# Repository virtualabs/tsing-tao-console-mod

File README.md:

# Tsing Tao v1 - a cheap ESP32 mod for a cheap handheld

Tsing Tao is a set of three tiny printed circuit boards that can turn any cheap
Chinese handheld gaming console (sold as Game Boy like console with 400+ NES
games) into a full-featured retro emulator able to run GameBoy, Game Gear, NES,
and Master System ROMs.

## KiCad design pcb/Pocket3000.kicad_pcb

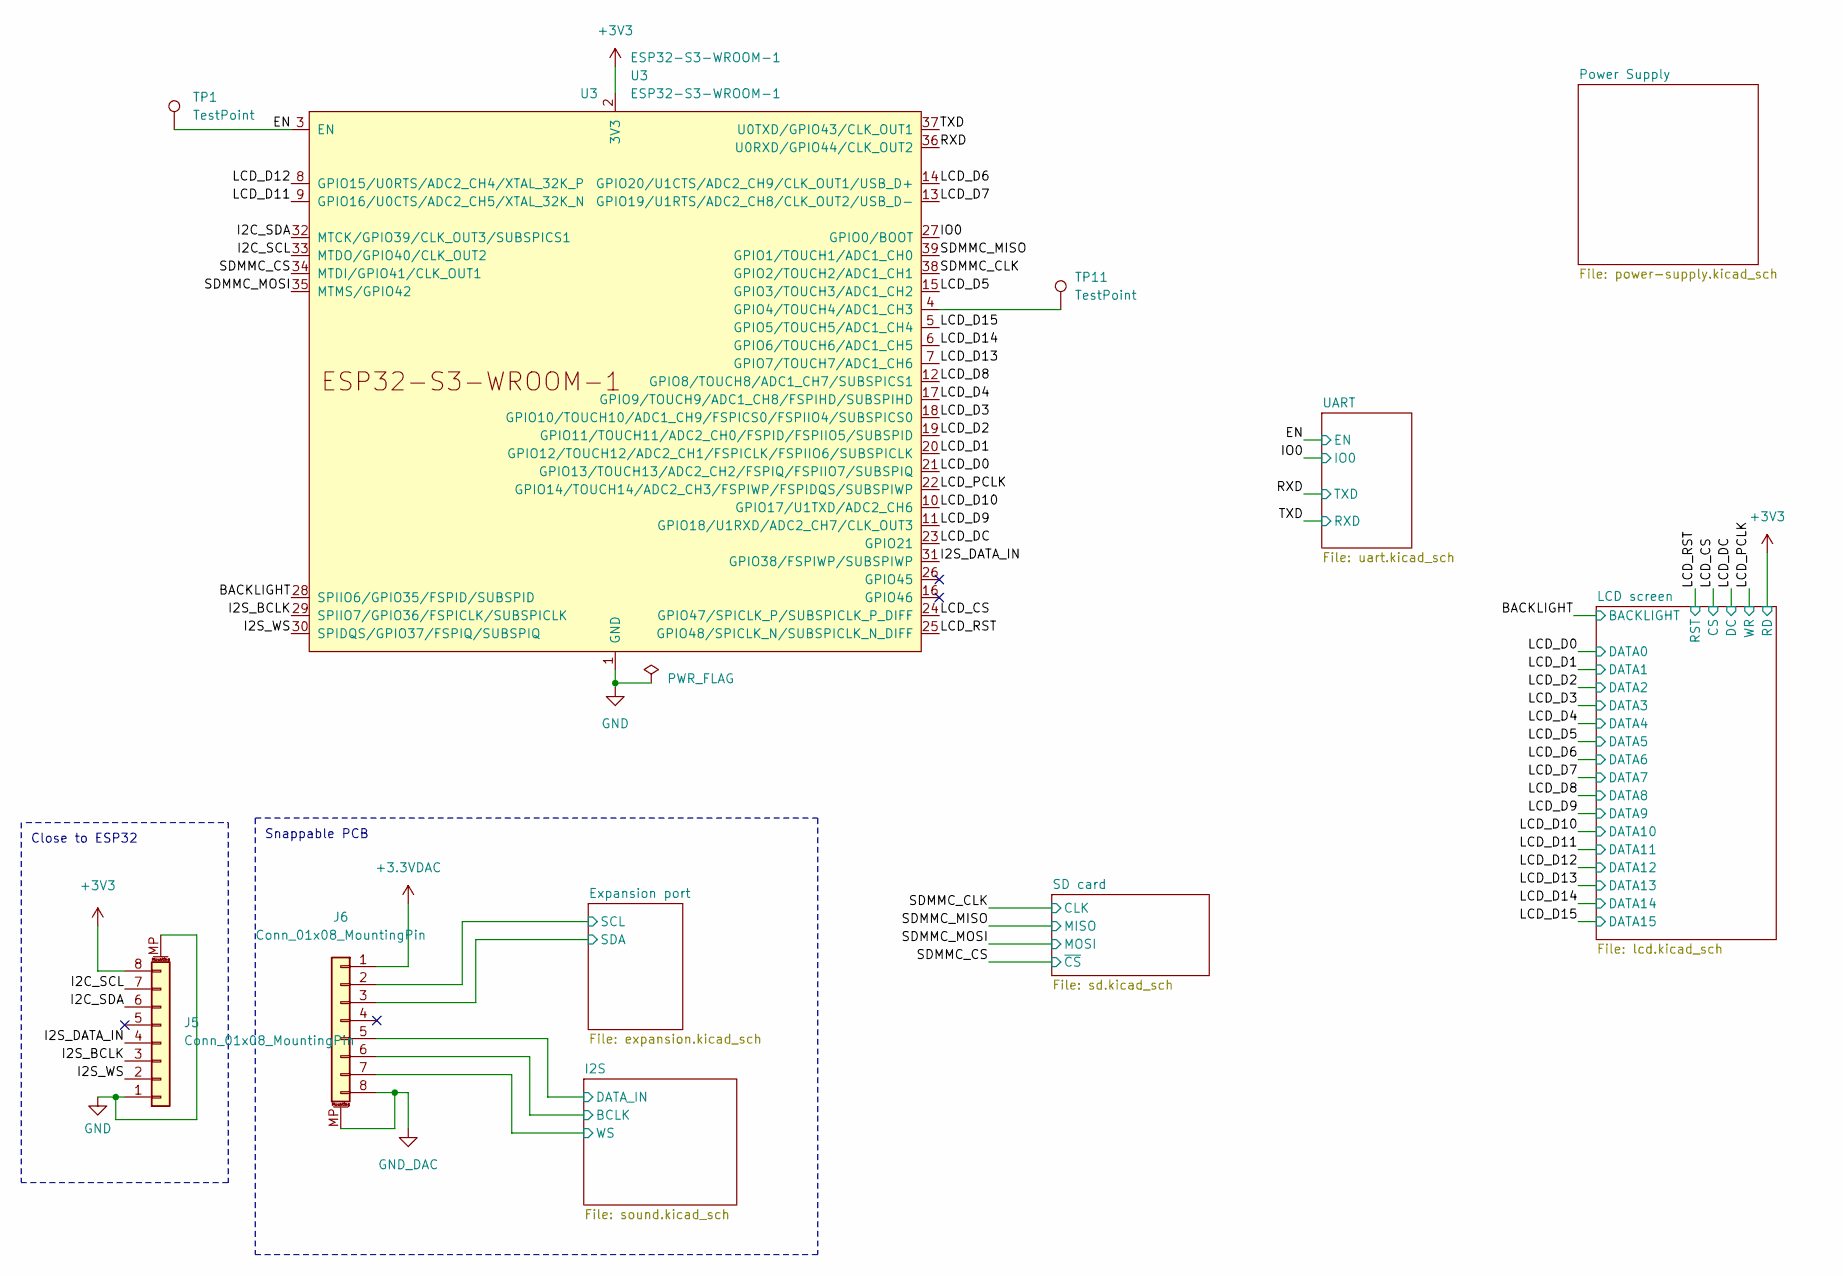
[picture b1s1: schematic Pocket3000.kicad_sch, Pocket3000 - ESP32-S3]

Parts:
J5, J6: Conn_01x08_MountingPin; Hirose_FH12-8S-0.5SH_1x08-1MP_P0.50mm_Horizontal
TP1, TP11: TestPoint; TestPoint_Pad_D1.5mm
U3: ESP32-S3-WROOM-1; ESP32-S3-WROOM-1U

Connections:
+3.3VDAC: J6.1; also elsewhere on the board
+3V3: J5.8, U3.2 (3V3); also elsewhere on the board
/BACKLIGHT: U3.28 (SPIIO6/GPIO35/FSPID/SUBSPID); also elsewhere on the board
/EN: TP1.1, U3.3 (EN); also elsewhere on the board
/Expansion port/SCL: J6.2; also elsewhere on the board
/Expansion port/SDA: J6.3; also elsewhere on the board
/I2C_SCL: J5.7, U3.33 (MTDO/GPIO40/CLK_OUT2)
/I2C_SDA: J5.6, U3.32 (MTCK/GPIO39/CLK_OUT3/SUBSPICS1)
/I2S/BCLK: J6.6; also elsewhere on the board
/I2S/DATA_IN: J6.5; also elsewhere on the board
/I2S/WS: J6.7; also elsewhere on the board
/I2S_BCLK: J5.3, U3.29 (SPIIO7/GPIO36/FSPICLK/SUBSPICLK)
/I2S_DATA_IN: J5.4, U3.31 (GPIO38/FSPIWP/SUBSPIWP)
/I2S_WS: J5.2, U3.30 (SPIDQS/GPIO37/FSPIQ/SUBSPIQ)
/IO0: U3.27 (GPIO0/BOOT); also elsewhere on the board
/LCD_CS: U3.24 (GPIO47/SPICLK_P/SUBSPICLK_P_DIFF); also elsewhere on the board
/LCD_D0: U3.21 (GPIO13/TOUCH13/ADC2_CH2/FSPIQ/FSPIIO7/S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); also elsewhere on the board
/LCD_D1: U3.20 (GPIO12/TOUCH12/ADC2_CH1/FSPICLK/FSPIIO6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); also elsewhere on the board
/LCD_D2: U3.19 (GPIO11/TOUCH11/ADC2_CH0/FSPID/FSPIIO5/S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); also elsewhere on the board
/LCD_D3: U3.18 (GPIO10/TOUCH10/ADC1_CH9/FSPICS0/FSPIIO4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); also elsewhere on the board
/LCD_D4: U3.17 (GPIO9/TOUCH9/ADC1_CH8/FSPIHD/SUBSPIHD); also elsewhere on the board
/LCD_D5: U3.15 (GPIO3/TOUCH3/ADC1_CH2); also elsewhere on the board
/LCD_D6: U3.14 (GPIO20/U1CTS/ADC2_CH9/CLK_OUT1/USB_D+); also elsewhere on the board
/LCD_D7: U3.13 (GPIO19/U1RTS/ADC2_CH8/CLK_OUT2/USB_D-); also elsewhere on the board
/LCD_D8: U3.12 (GPIO8/TOUCH8/ADC1_CH7/SUBSPICS1); also elsewhere on the board
/LCD_D9: U3.11 (GPIO18/U1RXD/ADC2_CH7/CLK_OUT3); also elsewhere on the board
/LCD_D10: U3.10 (GPIO17/U1TXD/ADC2_CH6); also elsewhere on the board
/LCD_D11: U3.9 (GPIO16/U0CTS/ADC2_CH5/XTAL_32K_N); also elsewhere on the board
/LCD_D12: U3.8 (GPIO15/U0RTS/ADC2_CH4/XTAL_32K_P); also elsewhere on the board
/LCD_D13: U3.7 (GPIO7/TOUCH7/ADC1_CH6); also elsewhere on the board
/LCD_D14: U3.6 (GPIO6/TOUCH6/ADC1_CH5); also elsewhere on the board
/LCD_D15: U3.5 (GPIO5/TOUCH5/ADC1_CH4); also elsewhere on the board
/LCD_DC: U3.23 (GPIO21); also elsewhere on the board
/LCD_PCLK: U3.22 (GPIO14/TOUCH14/ADC2_CH3/FSPIWP/FSPIDQS/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); also elsewhere on the board
/LCD_RST: U3.25 (GPIO48/SPICLK_N/SUBSPICLK_N_DIFF); also elsewhere on the board
/RXD: U3.36 (U0RXD/GPIO44/CLK_OUT2); also elsewhere on the board
/SDMMC_CLK: U3.38 (GPIO2/TOUCH2/ADC1_CH1); also elsewhere on the board
/SDMMC_CS: U3.34 (MTDI/GPIO41/CLK_OUT1); also elsewhere on the board
/SDMMC_MISO: U3.39 (GPIO1/TOUCH1/ADC1_CH0); also elsewhere on the board
/SDMMC_MOSI: U3.35 (MTMS/GPIO42); also elsewhere on the board
/TXD: U3.37 (U0TXD/GPIO43/CLK_OUT1); also elsewhere on the board
GND: J5.1, J5.MP (MountPin), U3.1 (GND), U3.40 (GND), U3.41 (GND); also elsewhere on the board
GND_DAC: J6.8, J6.MP (MountPin); also elsewhere on the board
unnamed: TP11.1, U3.4 (GPIO4/TOUCH4/ADC1_CH3)

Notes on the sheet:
Snappable PCB
Close to ESP32

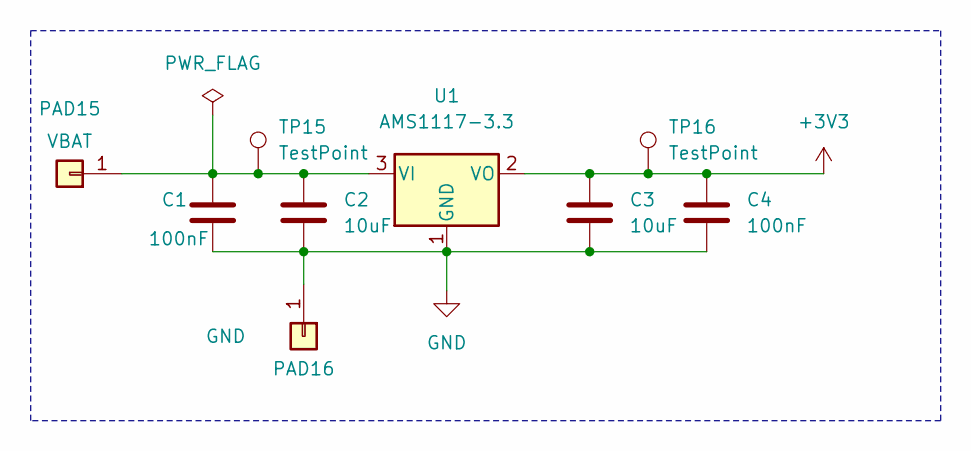
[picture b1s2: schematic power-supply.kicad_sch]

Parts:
C1: 100nF; C_0603_1608Metric
C2, C3: 10uF; C_0805_2012Metric
C4: 100nF; C_0805_2012Metric
PAD15: VBAT; TestPoint_Pad_2.0x2.0mm
PAD16: GND; TestPoint_Pad_2.0x2.0mm
TP15, TP16: TestPoint; TestPoint_Pad_D1.5mm
U1: AMS1117-3.3; SOT-223-3_TabPin2

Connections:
+3V3: C3.1, C4.1, TP16.1, U1.2 (VO); also elsewhere on the board
GND: C1.2, C2.2, C3.2, C4.2, PAD16.1, U1.1 (GND); also elsewhere on the board
unnamed: C1.1, C2.1, PAD15.1, TP15.1, U1.3 (VI)

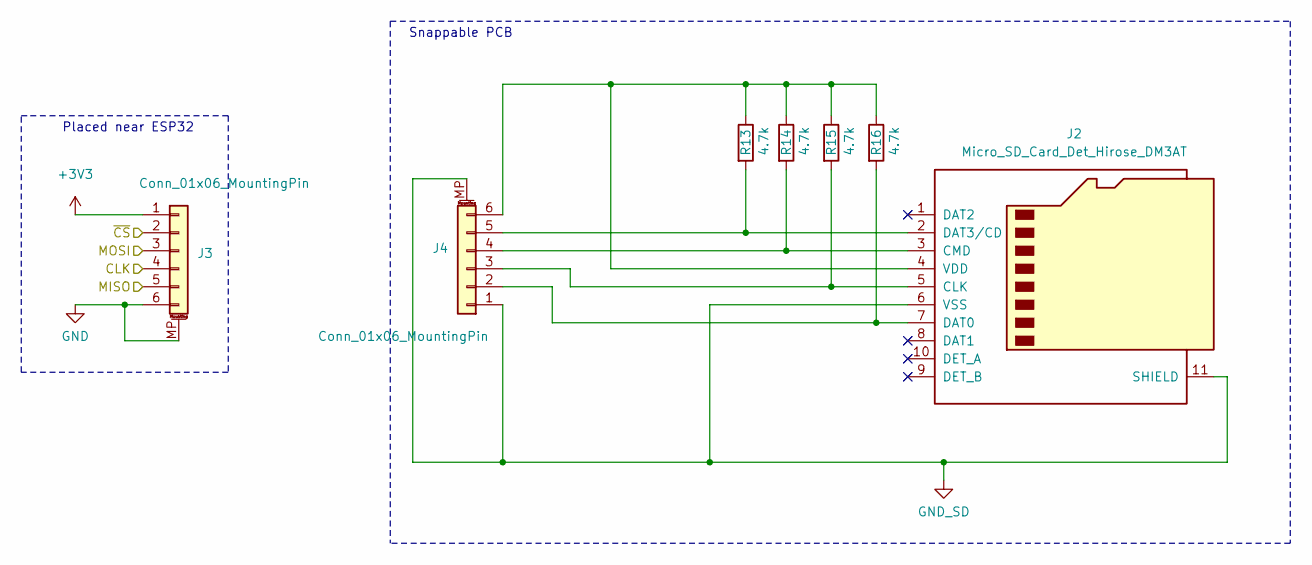
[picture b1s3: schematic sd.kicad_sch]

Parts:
J2: Micro_SD_Card_Det_Hirose_DM3AT; microSD_HC_Hirose_DM3AT-SF-PEJM5
J3, J4: Conn_01x06_MountingPin; Hirose_FH12-6S-0.5SH_1x06-1MP_P0.50mm_Horizontal
R13, R14, R15, R16: 4.7k; R_0603_1608Metric

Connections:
+3V3: J3.1; also elsewhere on the board
/SDMMC_CLK: J3.4; also elsewhere on the board
/SDMMC_CS: J3.2; also elsewhere on the board
/SDMMC_MISO: J3.5; also elsewhere on the board
/SDMMC_MOSI: J3.3; also elsewhere on the board
GND: J3.6, J3.MP (MountPin); also elsewhere on the board
GND_SD: J2.6 (VSS), J2.11 (SHIELD), J4.1, J4.MP (MountPin)
unnamed: J2.5 (CLK), J4.3, R15.2
unnamed: J2.3 (CMD), J4.4, R14.2
unnamed: J2.7 (DAT0), J4.2, R16.2
unnamed: J2.2 (DAT3/CD), J4.5, R13.2
unnamed: J2.4 (VDD), J4.6, R13.1, R14.1, R15.1, R16.1

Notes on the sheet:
Placed near ESP32
Snappable PCB

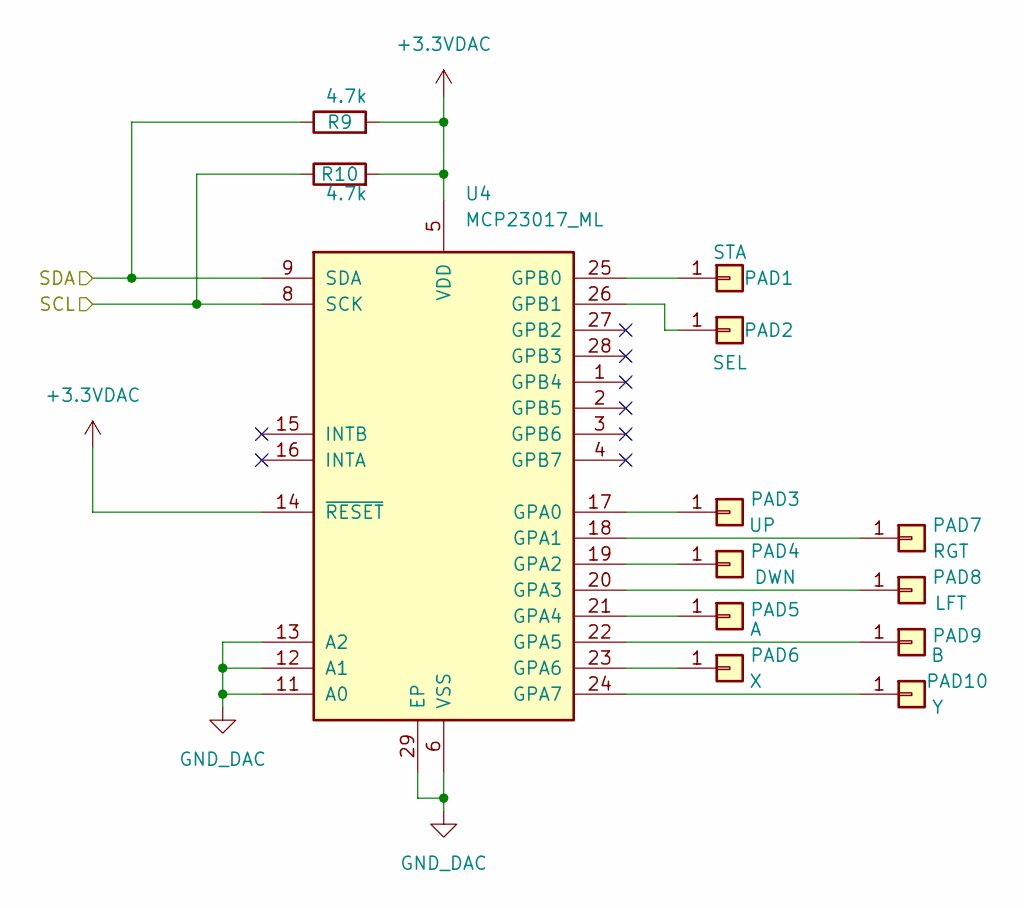
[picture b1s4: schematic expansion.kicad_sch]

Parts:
PAD1: STA; TestPoint_Pad_2.0x2.0mm
PAD2: SEL; TestPoint_Pad_2.0x2.0mm
PAD3: UP; TestPoint_Pad_2.0x2.0mm
PAD4: DWN; TestPoint_Pad_2.0x2.0mm
PAD5: A; TestPoint_Pad_2.0x2.0mm
PAD6: X; TestPoint_Pad_2.0x2.0mm
PAD7: RGT; TestPoint_Pad_2.0x2.0mm
PAD8: LFT; TestPoint_Pad_2.0x2.0mm
PAD9: B; TestPoint_Pad_2.0x2.0mm
PAD10: Y; TestPoint_Pad_2.0x2.0mm
R9, R10: 4.7k; R_0603_1608Metric
U4: MCP23017_ML; QFN-28-1EP_6x6mm_P0.65mm_EP4.25x4.25mm

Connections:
+3.3VDAC: R9.2, R10.2, U4.5 (VDD), U4.14 (~RESET); also elsewhere on the board
/Expansion port/SCL: R10.1, U4.8 (SCK); also elsewhere on the board
/Expansion port/SDA: R9.1, U4.9 (SDA); also elsewhere on the board
GND_DAC: U4.6 (VSS), U4.11 (A0), U4.12 (A1), U4.13 (A2), U4.29 (EP); also elsewhere on the board
unnamed: PAD1.1, U4.25 (GPB0)
unnamed: PAD2.1, U4.26 (GPB1)
unnamed: PAD3.1, U4.17 (GPA0)
unnamed: PAD4.1, U4.19 (GPA2)
unnamed: PAD5.1, U4.21 (GPA4)
unnamed: PAD6.1, U4.23 (GPA6)
unnamed: PAD7.1, U4.18 (GPA1)
unnamed: PAD8.1, U4.20 (GPA3)
unnamed: PAD9.1, U4.22 (GPA5)
unnamed: PAD10.1, U4.24 (GPA7)

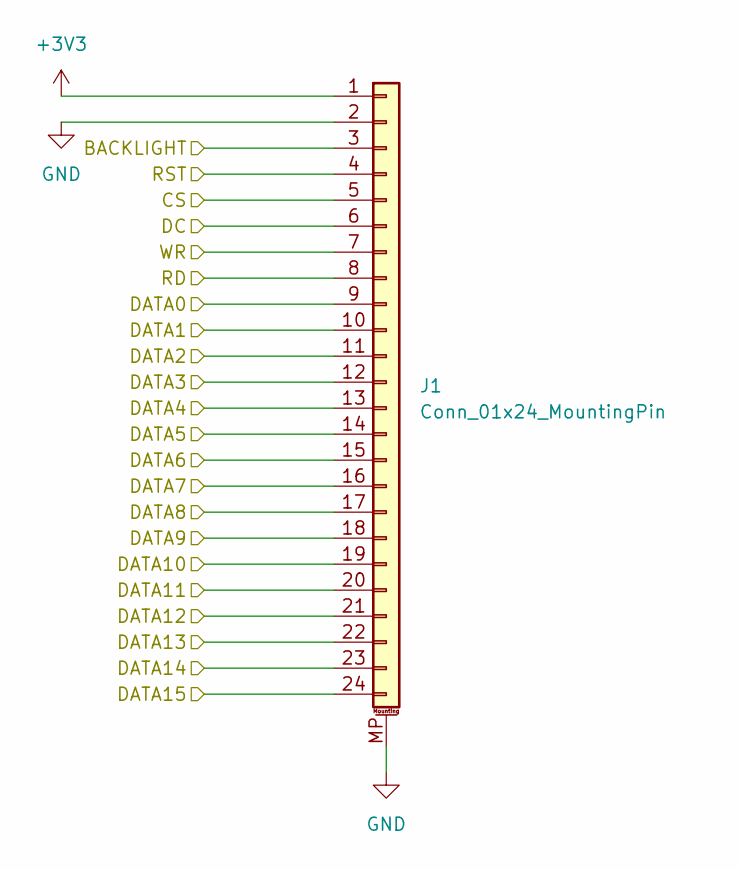
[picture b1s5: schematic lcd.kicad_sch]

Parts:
J1: Conn_01x24_MountingPin; Hirose_FH12-24S-0.5SH_1x24-1MP_P0.50mm_Horizontal

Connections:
+3V3: J1.1, J1.8; also elsewhere on the board
/BACKLIGHT: J1.3; also elsewhere on the board
/LCD_CS: J1.5; also elsewhere on the board
/LCD_D0: J1.9; also elsewhere on the board
/LCD_D1: J1.10; also elsewhere on the board
/LCD_D2: J1.11; also elsewhere on the board
/LCD_D3: J1.12; also elsewhere on the board
/LCD_D4: J1.13; also elsewhere on the board
/LCD_D5: J1.14; also elsewhere on the board
/LCD_D6: J1.15; also elsewhere on the board
/LCD_D7: J1.16; also elsewhere on the board
/LCD_D8: J1.17; also elsewhere on the board
/LCD_D9: J1.18; also elsewhere on the board
/LCD_D10: J1.19; also elsewhere on the board
/LCD_D11: J1.20; also elsewhere on the board
/LCD_D12: J1.21; also elsewhere on the board
/LCD_D13: J1.22; also elsewhere on the board
/LCD_D14: J1.23; also elsewhere on the board
/LCD_D15: J1.24; also elsewhere on the board
/LCD_DC: J1.6; also elsewhere on the board
/LCD_PCLK: J1.7; also elsewhere on the board
/LCD_RST: J1.4; also elsewhere on the board
GND: J1.2, J1.MP (MountPin); also elsewhere on the board

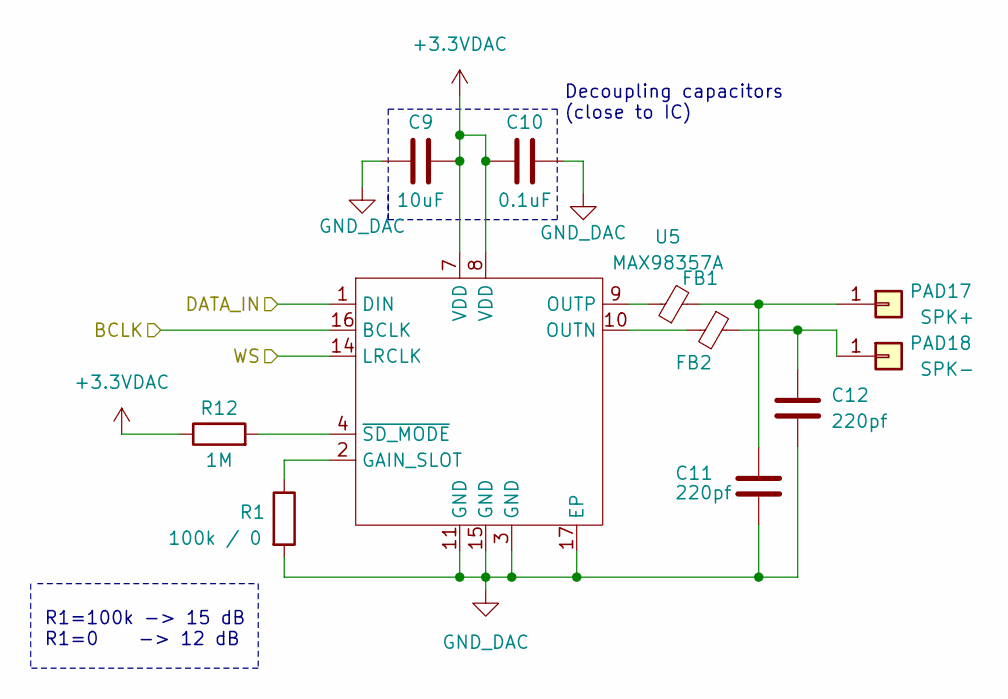
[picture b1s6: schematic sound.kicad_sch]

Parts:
C9: 10uF; C_0603_1608Metric
C10: 0.1uF; C_0603_1608Metric
C11, C12: 220pf; C_0603_1608Metric
FB1, FB2: FerriteBead_Small; L_0805_2012Metric
PAD17: SPK+; TestPoint_Pad_2.0x2.0mm
PAD18: SPK-; TestPoint_Pad_2.0x2.0mm
R1: 100k / 0; R_0805_2012Metric
R12: 1M; R_0805_2012Metric
U5: MAX98357A; TQFN-16-1EP_3x3mm_P0.5mm_EP1.23x1.23mm

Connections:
+3.3VDAC: C9.2, C10.1, R12.1, U5.7 (VDD), U5.8 (VDD); also elsewhere on the board
/I2S/BCLK: U5.16 (BCLK); also elsewhere on the board
/I2S/DATA_IN: U5.1 (DIN); also elsewhere on the board
/I2S/WS: U5.14 (LRCLK); also elsewhere on the board
GND_DAC: C9.1, C10.2, C11.2, C12.2, R1.2, U5.3 (GND), U5.11 (GND), U5.15 (GND), U5.17 (EP); also elsewhere on the board
unnamed: C11.1, FB1.2, PAD17.1
unnamed: C12.1, FB2.1, PAD18.1
unnamed: R1.1, U5.2 (GAIN_SLOT)
unnamed: FB2.2, U5.10 (OUTN)
unnamed: FB1.1, U5.9 (OUTP)
unnamed: R12.2, U5.4 (~SD_MODE)

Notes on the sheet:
Decoupling capacitors (close to IC)
R1=100k -> 15 dB R1=0 -> 12 dB

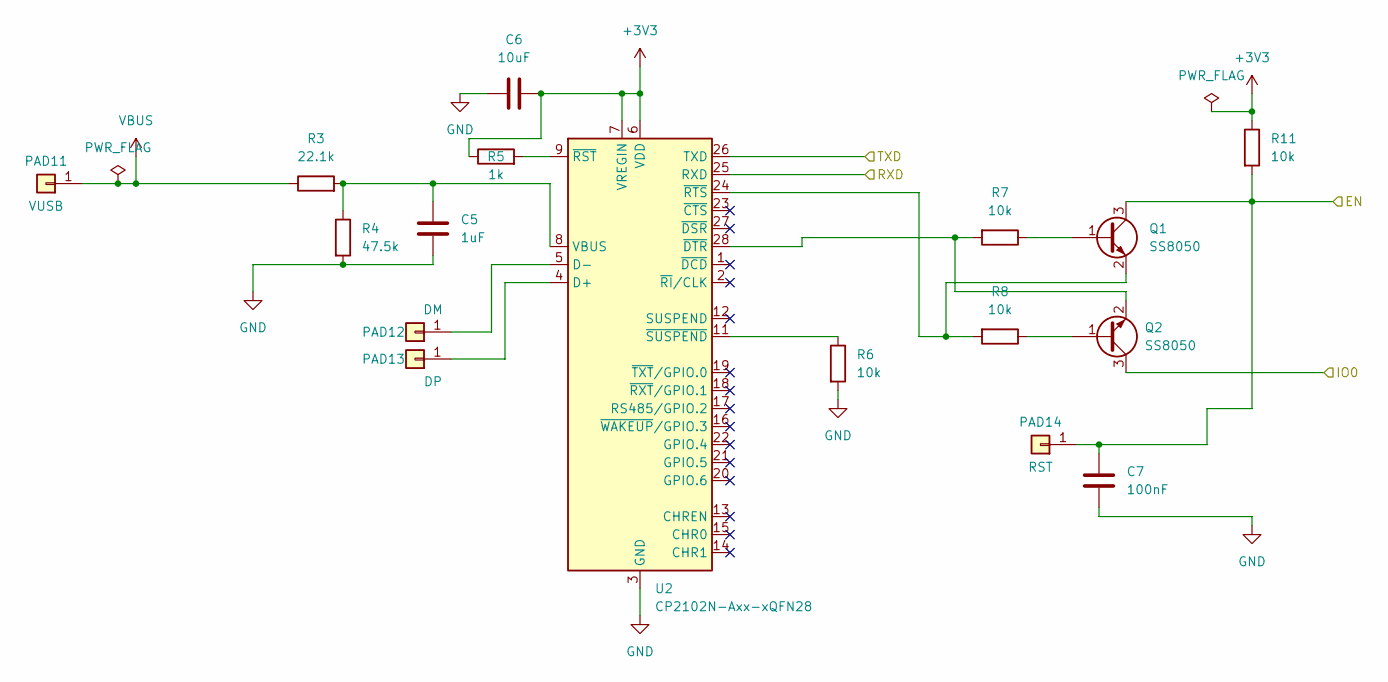
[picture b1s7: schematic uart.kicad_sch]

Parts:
C5: 1uF; C_0805_2012Metric
C6: 10uF; C_0805_2012Metric
C7: 100nF; C_0603_1608Metric
PAD11: VUSB; TestPoint_Pad_2.0x2.0mm
PAD12: DM; TestPoint_Pad_2.0x2.0mm
PAD13: DP; TestPoint_Pad_2.0x2.0mm
PAD14: RST; TestPoint_Pad_2.0x2.0mm
Q1, Q2: SS8050; SOT-23-3
R3: 22.1k; R_0603_1608Metric
R4: 47.5k; R_0603_1608Metric
R5: 1k; R_0603_1608Metric
R6, R7, R8, R11: 10k; R_0603_1608Metric
U2: CP2102N-Axx-xQFN28; QFN-28-1EP_5x5mm_P0.5mm_EP3.35x3.35mm

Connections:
+3V3: C6.2, R5.1, R11.1, U2.6 (VDD), U2.7 (VREGIN); also elsewhere on the board
/EN: C7.1, PAD14.1, Q1.3 (C), R11.2; also elsewhere on the board
/IO0: Q2.3 (C); also elsewhere on the board
/RXD: U2.26 (TXD); also elsewhere on the board
/TXD: U2.25 (RXD); also elsewhere on the board
GND: C5.2, C6.1, C7.2, R4.2, R6.2, U2.3 (GND), U2.29 (GND); also elsewhere on the board
unnamed: PAD12.1, U2.5 (D-)
unnamed: PAD13.1, U2.4 (D+)
unnamed: Q1.1 (B), R7.1
unnamed: Q1.2 (E), R8.2, U2.24 (~RTS)
unnamed: Q2.1 (B), R8.1
unnamed: Q2.2 (E), R7.2, U2.28 (~DTR)
unnamed: C5.1, R3.2, R4.1, U2.8 (VBUS)
unnamed: R5.2, U2.9 (~RST)
unnamed: R6.1, U2.11 (~SUSPEND)
VBUS: PAD11.1, R3.1

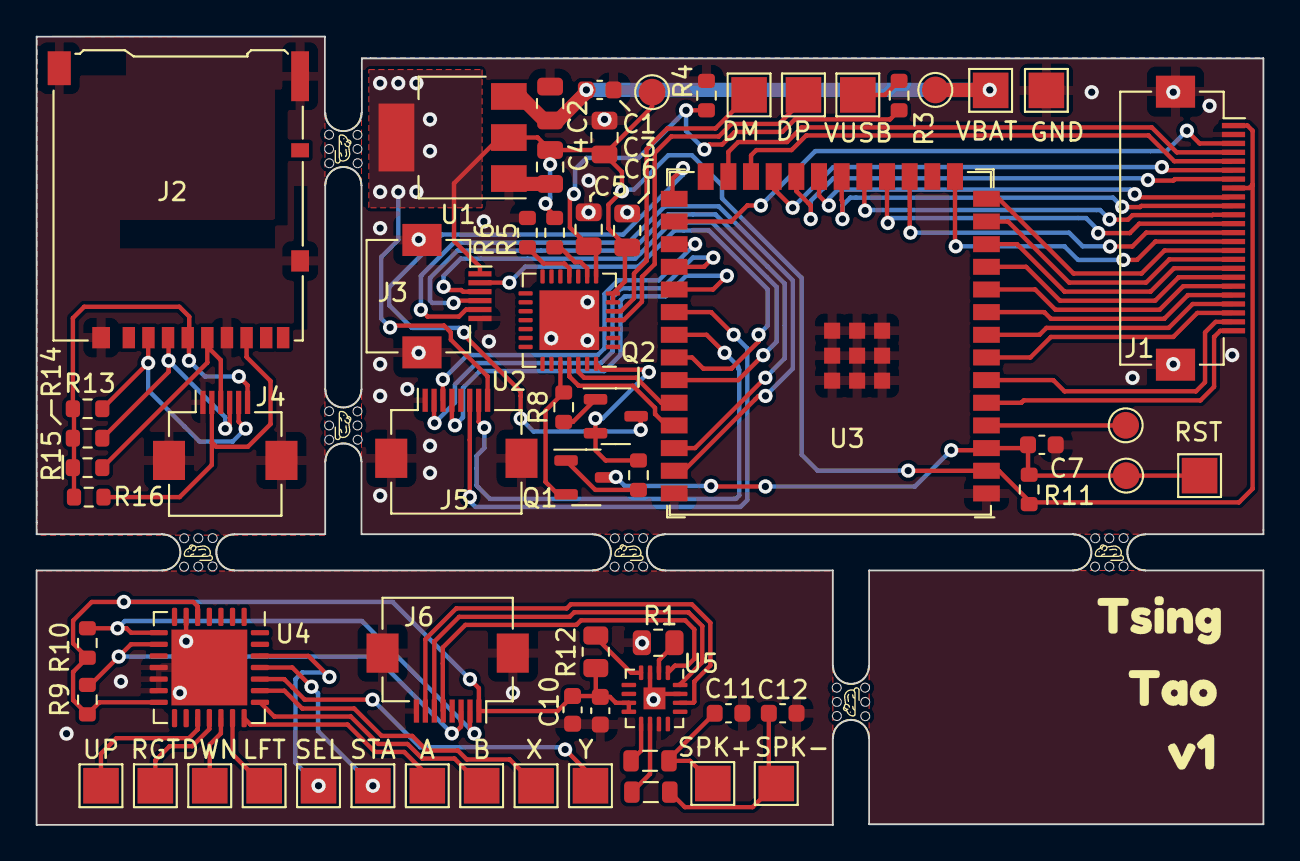
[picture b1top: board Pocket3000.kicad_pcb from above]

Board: 2 copper layers, 68.8 x 44.2 mm, 72 parts (0 on the bottom side), 77 nets.

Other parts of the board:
kibuzzard-693B4E6F: G***; kibuzzard-693B4E6F
kibuzzard-693B4E49: G***; kibuzzard-693B4E49
kibuzzard-693B4E54: G***; kibuzzard-693B4E54
mouse-bite-2mm-4mm, mouse-bite-2mm-4mm#2, mouse-bite-2mm-4mm#3, mouse-bite-2mm-4mm#4, mouse-bite-2mm-4mm#5, mouse-bite-2mm-4mm#6: VAL**; mouse-bite-2mm-4mm

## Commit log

2025-12-11 First commit.
2025-12-16 Added docs folder.
2025-12-16 Fixed submodule error.
2025-12-16 New test site.
2025-12-16 First version (WIP) of the project documentation.
2025-12-17 Added missing just-the-docs dependency.
2025-12-17 Updated just-the-docs template
2025-12-17 Added gitignore.
2025-12-17 Another attempt at getting the just-the-docs template working.
2025-12-17 Updated actions workflow.
2025-12-17 Added missing Gemfile
2025-12-17 Modified github workflow to build using jekyll.
2025-12-17 Fixed docs path.
2025-12-17 Updated workflow.
2025-12-17 Fixed workflow to use the docs folder.
2025-12-17 Fixed typos.
2025-12-17 Test
2025-12-18 Added PCB assembly and gerber zip file.
2025-12-18 Added Retro-Go flashing instructions.
2025-12-18 Fixed typo.
2025-12-18 Added some extra text.
